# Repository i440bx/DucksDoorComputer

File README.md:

###Why no more infos?
This PCB RevB has some errata:
1) Small routing error for 5V rails
2) Heavy footprint error for StepUp/StepDown converters
3) Used old items from Adafruit/AZ-Delivery/China-guys wich are not available anymore

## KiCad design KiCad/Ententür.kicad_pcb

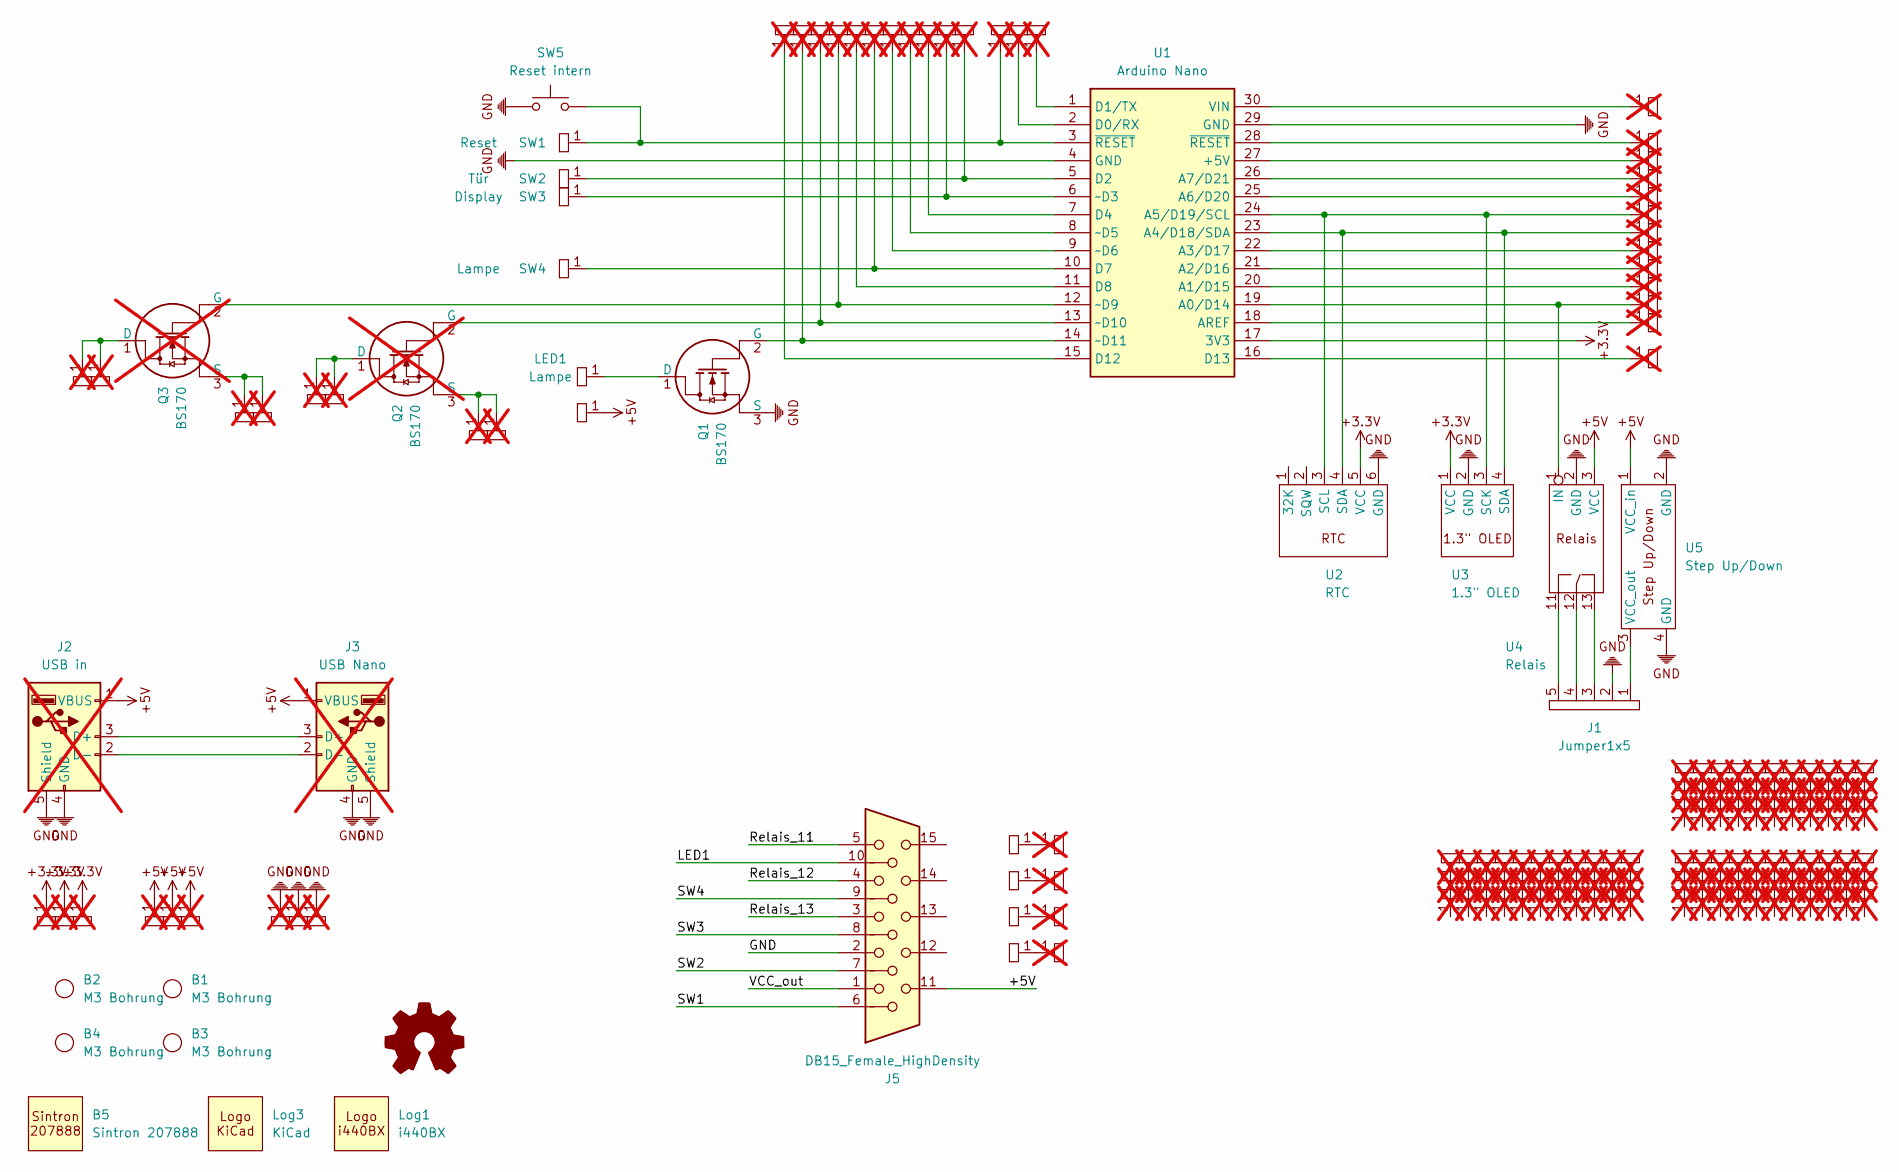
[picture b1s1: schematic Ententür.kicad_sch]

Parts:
B1, B2, B3, B4: M3 Bohrung
B5: Sintron 207888
J1: Jumper1x5; JP, 1x5, stehend, P2.54
J2: USB in; JP, 1x4, stehend, P2.54; not fitted
J3: USB Nano; JP, 1x4, stehend, P2.54; not fitted
J5: DB15_Female_HighDensity
LED1: Lampe; JP, 1x1, stehend, P2.54
Log1: i440BX; Logo i440BX
Log2: Open Hardware; Logo OSHW
Log3: KiCad; Logo KiCad
Q1: BS170; TO92.3, Inline, Stehend
Q2, Q3: BS170; TO92.3, Inline, Stehend; not fitted
ST1, ST2, ST3, ST4, ST5, ST6, ST7, ST8, ST9, ST10, ST11, ST12, ST13, ST14, ST15, ST16, ST17, ST18, ST19, ST20, ST21, ST22, ST23, ST24, ST25, ST43, ST44, ST45, ST46, ST47, ST48, ST49, ST50, ST51, ST52, ST53, ST54, ST55, ST56, ST57, ST58, ST59, ST60, ST61, ST62, ST63, ST64, ST65, ST66, ST67, ST68, ST69, ST70, ST71, ST72, ST73, ST74, ST75, ST76, ST77, ST78, ST79, ST80, ST81, ST82, ST83, ST84, ST85, ST86, ST87, ST88, ST89, ST90, ST91, ST92, ST93, ST94, ST95, ST96, ST97, ST98, ST99, ST100, ST101, ST102, ST103, ST104, ST105, ST106, ST107, ST108, ST109, ST110, ST111, ST112, ST113, ST114, ST115, ST116, ST117, ST118, ST119, ST120, ST121, ST122, ST123, ST124, ST125, ST126, ST127, ST128, ST129, ST130, ST131, ST132, ST133, ST134, ST135, ST136, ST137, ST138, ST139, ST140, ST141, ST142, ST188, ST189, ST190, ST191, ST192, ST193, ST194, ST195, ST196: Jumper1x1; JP, 1x1, stehend, P2.54, ohne Slikscreen; not fitted
ST26, ST27, ST28, ST36, ST38, ST40, ST42: GND; JP, 1x1, stehend, P2.54, ohne Slikscreen; not fitted
ST29, ST30, ST31: 5V; JP, 1x1, stehend, P2.54, ohne Slikscreen; not fitted
ST32, ST33, ST34: 3.3V; JP, 1x1, stehend, P2.54, ohne Slikscreen; not fitted
ST35, ST37, ST39, ST41: GND; JP, 1x1, stehend, P2.54, ohne Slikscreen
ST197: 5V; JP, 1x1, stehend, P2.54, ohne Slikscreen
SW1: Reset; JP, 1x1, stehend, P2.54
SW2: Tür; JP, 1x1, stehend, P2.54
SW3: Display; JP, 1x1, stehend, P2.54
SW4: Lampe; JP, 1x1, stehend, P2.54
SW5: Reset intern; JP, 1x2, stehend, P2.54
U1: Arduino Nano
U2: RTC; AZ-Delivery RTC
U3: 1.3" OLED; AZ-Delivery 1.3 OLED
U4: Relais; AZ-Delivery Relais (2x Pinheader)
U5: Step Up/Down; AZ-Delivery Step UpDown

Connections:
0V: J1.2, J2.4 (GND), J2.5 (Shield), J3.4 (GND), J3.5 (Shield), Q1.3 (S), ST26.1, ST27.1, ST28.1, SW5.1, U1.4 (GND), U1.29 (GND), U2.6 (GND), U3.2 (GND), U4.2 (GND), U5.2 (GND), U5.4 (GND)
+3.3V: ST32.1, ST33.1, ST34.1, U1.17 (3V3), U2.5 (VCC), U3.1 (VCC)
+5V: J2.1 (VBUS), J3.1 (VBUS), ST29.1, ST30.1, ST31.1, ST197.1, U4.3 (VCC), U5.1 (VCC_in)
unnamed: J1.3, U4.13
unnamed: J1.4, U4.12
unnamed: J1.5, U4.11
unnamed: J2.3 (D+), J3.3 (D+)
unnamed: J2.2 (D-), J3.2 (D-)
unnamed: LED1.1, Q1.1 (D)
unnamed: Q1.2 (G), ST25.1, U1.14 (~D11)
unnamed: Q2.1 (D), ST189.1, ST191.1
unnamed: Q2.2 (G), ST15.1, U1.13 (~D10)
unnamed: Q2.3 (S), ST188.1, ST190.1
unnamed: Q3.1 (D), ST192.1, ST194.1
unnamed: Q3.2 (G), ST14.1, U1.12 (~D9)
unnamed: Q3.3 (S), ST195.1, ST196.1
unnamed: ST1.1, U1.28 (~RESET)
unnamed: ST20.1, SW1.1, SW5.2, U1.3 (~RESET)
unnamed: ST35.1, ST36.1
unnamed: ST37.1, ST38.1
unnamed: ST39.1, ST40.1
unnamed: ST41.1, ST42.1
unnamed: ST43.1, U1.27 (+5V)
unnamed: ST19.1, U1.19 (A0/D14), U4.1 (IN)
unnamed: ST7.1, U1.20 (A1/D15)
unnamed: ST6.1, U1.21 (A2/D16)
unnamed: ST5.1, U1.22 (A3/D17)
unnamed: ST18.1, U1.23 (A4/D18/SDA), U2.4 (SDA), U3.4 (SDA)
unnamed: ST17.1, U1.24 (A5/D19/SCL), U2.3 (SCL), U3.3 (SCK)
unnamed: ST4.1, U1.25 (A6/D20)
unnamed: ST3.1, U1.26 (A7/D21)
unnamed: ST8.1, U1.18 (AREF)
unnamed: ST11.1, U1.2 (D0/RX)
unnamed: ST10.1, U1.1 (D1/TX)
unnamed: ST193.1, SW2.1, U1.5 (D2)
unnamed: ST12.1, U1.7 (D4)
unnamed: ST24.1, SW4.1, U1.10 (D7)
unnamed: ST13.1, U1.11 (D8)
unnamed: ST16.1, U1.15 (D12)
unnamed: ST9.1, U1.16 (D13)
unnamed: ST2.1, U1.30 (VIN)
unnamed: ST21.1, SW3.1, U1.6 (~D3)
unnamed: ST22.1, U1.8 (~D5)
unnamed: ST23.1, U1.9 (~D6)
unnamed: J1.1, U5.3 (VCC_out)

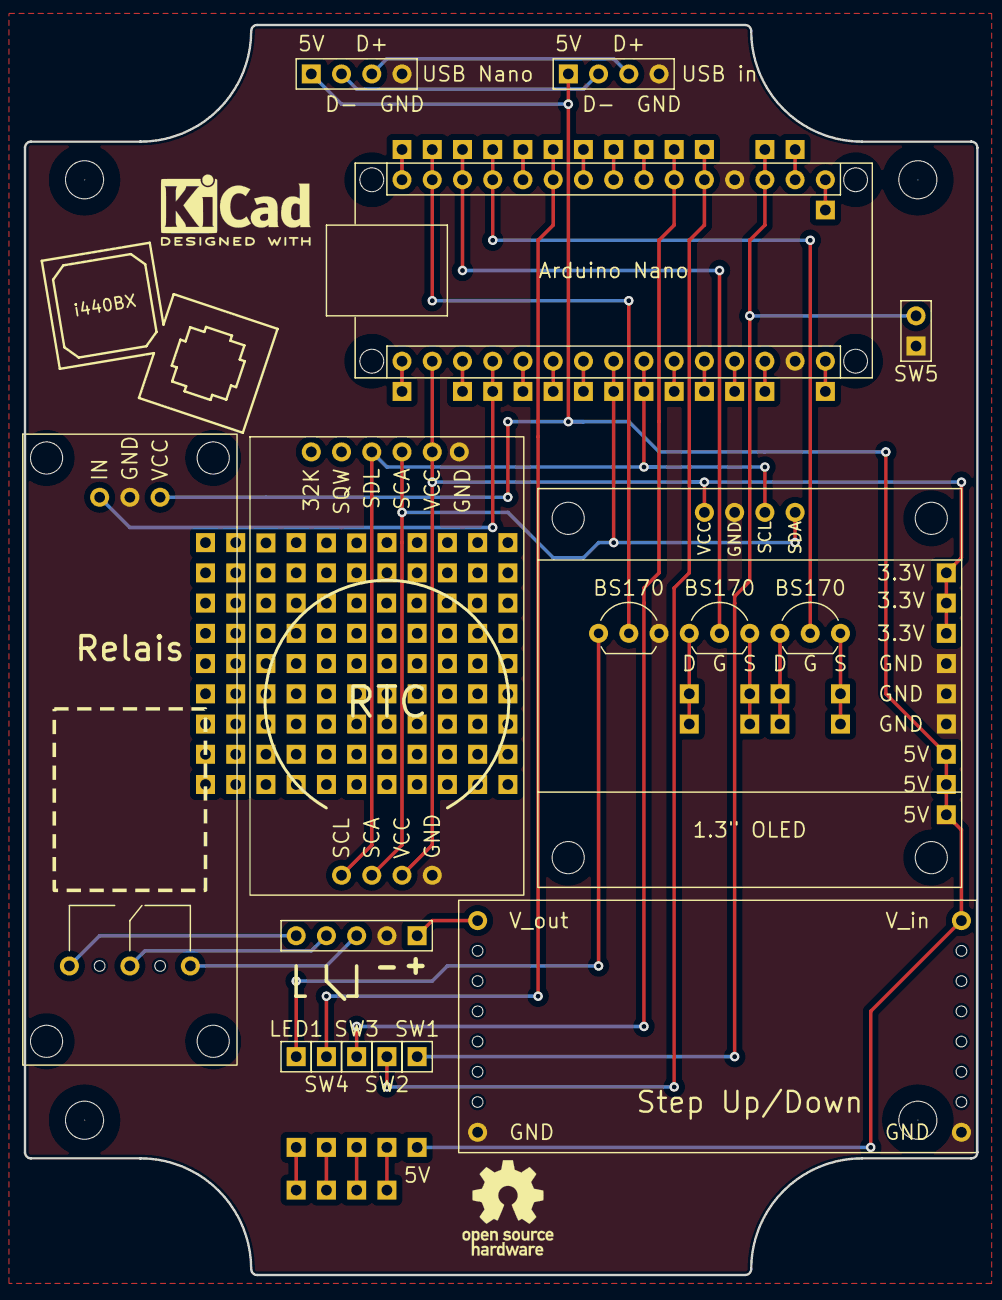
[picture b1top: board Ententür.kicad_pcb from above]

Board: 2 copper layers, 80.0 x 105.0 mm, 177 parts (0 on the bottom side), 45 nets.
